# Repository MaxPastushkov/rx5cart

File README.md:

# RX5Cart
A replacement for the Yamaha RAM4 cartridge, based on [GliGli's RX5USB](https://github.com/gligli/rx5usb)

**WARNING: This project is currently incomplete. Do not use the board yet! The PCB and firmware have not been tested!**

* `board_sch` - board and schematic files for KiCad
* `rx5cart.ino` - firmware for the teensy
* `transfer.py` - software for interfacing to the RX5Cart

### Loading the firmware ###
You will need Teensyduino. Download and instructions are [here](https://www.pjrc.com/teensy/td_download.html).

Open the `rx5cart.ino` file in the Arduino software, plug in the teensy, and press Upload.

### Using the transfer software ###
* You will need Python 3 and the `pyserial` package.
* To read RAM into a file, use `python transfer.py -r file.bin`
* To write to RAM from a file, use `python transfer.py -w file.bin`
* By default it uses the device `/dev/ttyACM0`. You can use the `-d` flag to change it.

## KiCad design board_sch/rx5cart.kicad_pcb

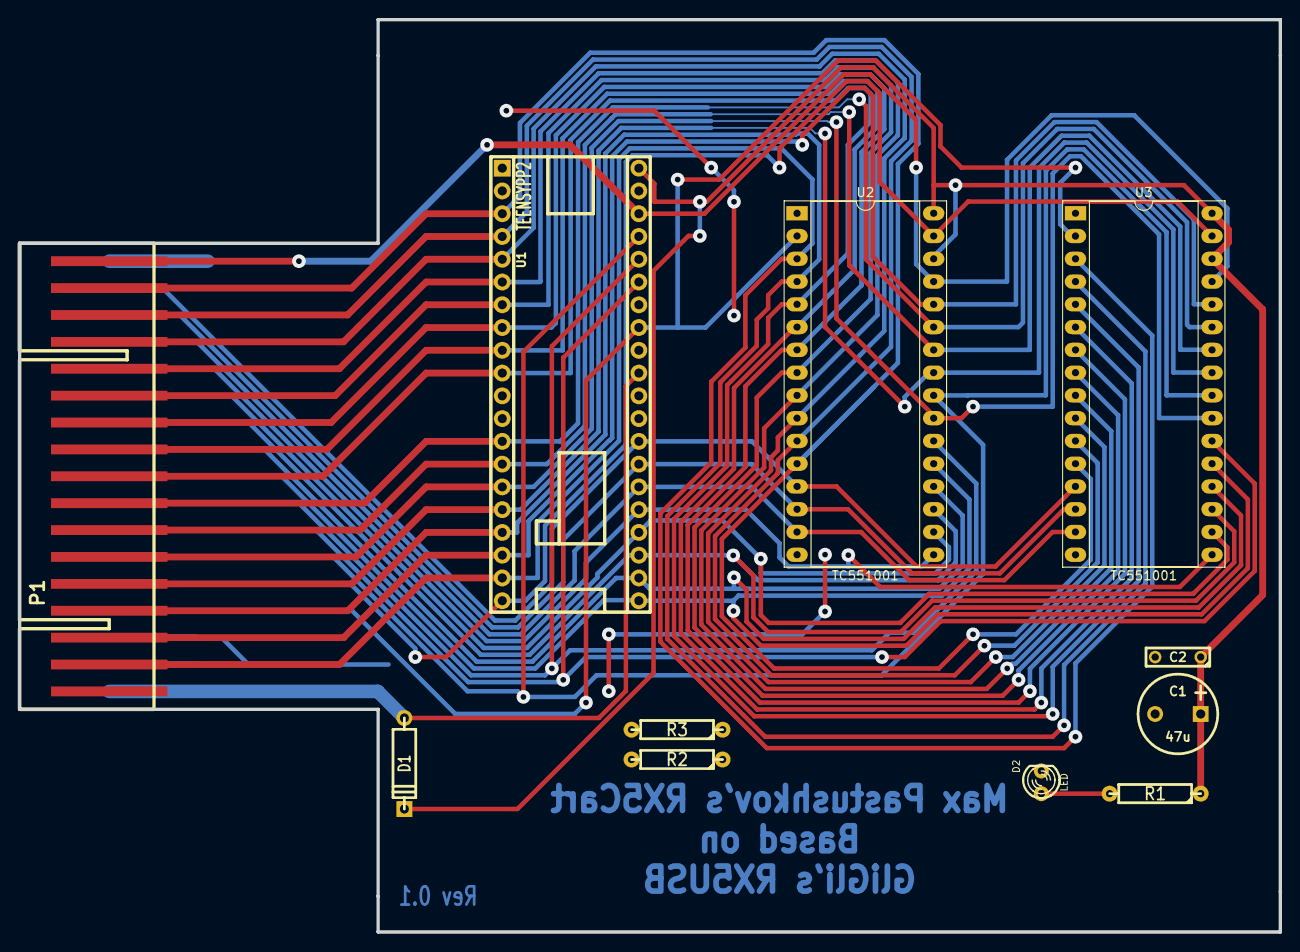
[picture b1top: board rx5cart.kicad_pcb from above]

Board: 2 copper layers, 140.7 x 101.8 mm, 11 parts (0 on the bottom side), 33 nets.

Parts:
C1: 47u; C1
C2: 100n; C2
D1: 1N5817
D2: LED; LED-3MM
P1: RX5_WDC; RX5_WDC_CART
R1: 470; RESISTOR
R2, R3: 10k; RESISTOR
U1: TEENSYPP2
U2, U3: TC551001

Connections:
/A0: P1.A0, U1.3, U2.12, U3.12
/A1: P1.A1, U1.4, U2.11, U3.11
/A2: P1.A2, U1.5, U2.10, U3.10
/A3: P1.A3, U1.6, U2.9, U3.9
/A4: P1.A4, U1.7, U2.8, U3.8
/A5: P1.A5, U1.8, U2.7, U3.7
/A6: P1.A6, U1.9, U2.6, U3.6
/A7: P1.A7, U1.10, U2.5, U3.5
/A8: P1.A8, U1.13, U2.27, U3.27
/A9: P1.A9, U1.14, U2.26, U3.26
/A10: P1.A10, U1.15, U2.23, U3.23
/A11: P1.A11, U1.16, U2.25, U3.25
/A12: P1.A12, U1.17, U2.4, U3.4
/A13: P1.A13, U1.18, U2.28, U3.28
/A14: P1.A14, U1.19, U2.3, U3.3
/A15: P1.A15, U1.20, U2.31, U3.31
/A16: P1.A16, U1.45, U2.2, U3.2
/CE0: P1.CE0, R3.1, U1.48, U2.22
/CE1: P1.CE1, R2.1, U1.47, U3.22
/D0: P1.D0, U1.40, U2.13, U3.13
/D1: P1.D1, U1.39, U2.14, U3.14
/D2: P1.D2, U1.38, U2.15, U3.15
/D3: P1.D3, U1.37, U2.17, U3.17
/D4: P1.D4, U1.36, U2.18, U3.18
/D5: P1.D5, U1.35, U2.19, U3.19
/D6: P1.D6, U1.34, U2.20, U3.20
/D7: P1.D7, U1.33, U2.21, U3.21
/OE: P1.OE, U1.49, U2.24, U3.24
/WE: P1.WE, U1.50, U2.29, U3.29
GND: C1.2, C2.2, D2.2, P1.CT0, P1.CT1, P1.GND, U1.1, U1.42, U2.16, U3.16
unnamed: D1.1, P1.+5V, U1.43
unnamed: D2.1, R1.2
VCC: C1.1, C2.1, D1.2, R1.1, R2.2, R3.2, U1.52, U2.30, U2.32, U3.30, U3.32

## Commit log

2021-08-27 Add all files
2021-08-28 Add RX5 power sense
2021-08-31 somewhat final
2021-08-31 Add progress bar
2021-08-31 Untested code
2021-08-31 Change revision number
2021-08-31 Fixed extra paste layer
2021-08-31 Generate gerbers
2021-08-31 Add gitignore
2021-09-02 Change ground plane
2021-10-21 Fix multiple issues
2021-10-21 Unfinished PCB
